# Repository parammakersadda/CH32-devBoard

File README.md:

# CH32X033F8P6 Development Board

## Purpose

This project was developed by **Param Makers Adda** to provide an open hardware development board based on the **CH32X033F8P6** microcontroller. The design is intended to be studied, modified, manufactured, and improved by anyone under the terms of the CERN Open Hardware Licence Version 2 – Weakly Reciprocal (CERN-OHL-W v2).

Copyright © 2026 Param Makers Adda

This hardware is licensed under the CERN Open Hardware Licence Version 2 – Weakly Reciprocal (CERN-OHL-W v2).

See the `LICENSE` file for the full license text.

## Images

[PCB routing](PDFs/pcb-routing.pdf)  

[Schematic](PDFs/ch32-devboard.pdf)

[3d rendering](3dModels/3dModel.stl)

## Exports

check `exports` folder for pcb export  

check the [`panelisedPcb`](panelisedPcb/) folder for panelised(multiple copies in a single board, for manufacturing purpose) pcb gerber export

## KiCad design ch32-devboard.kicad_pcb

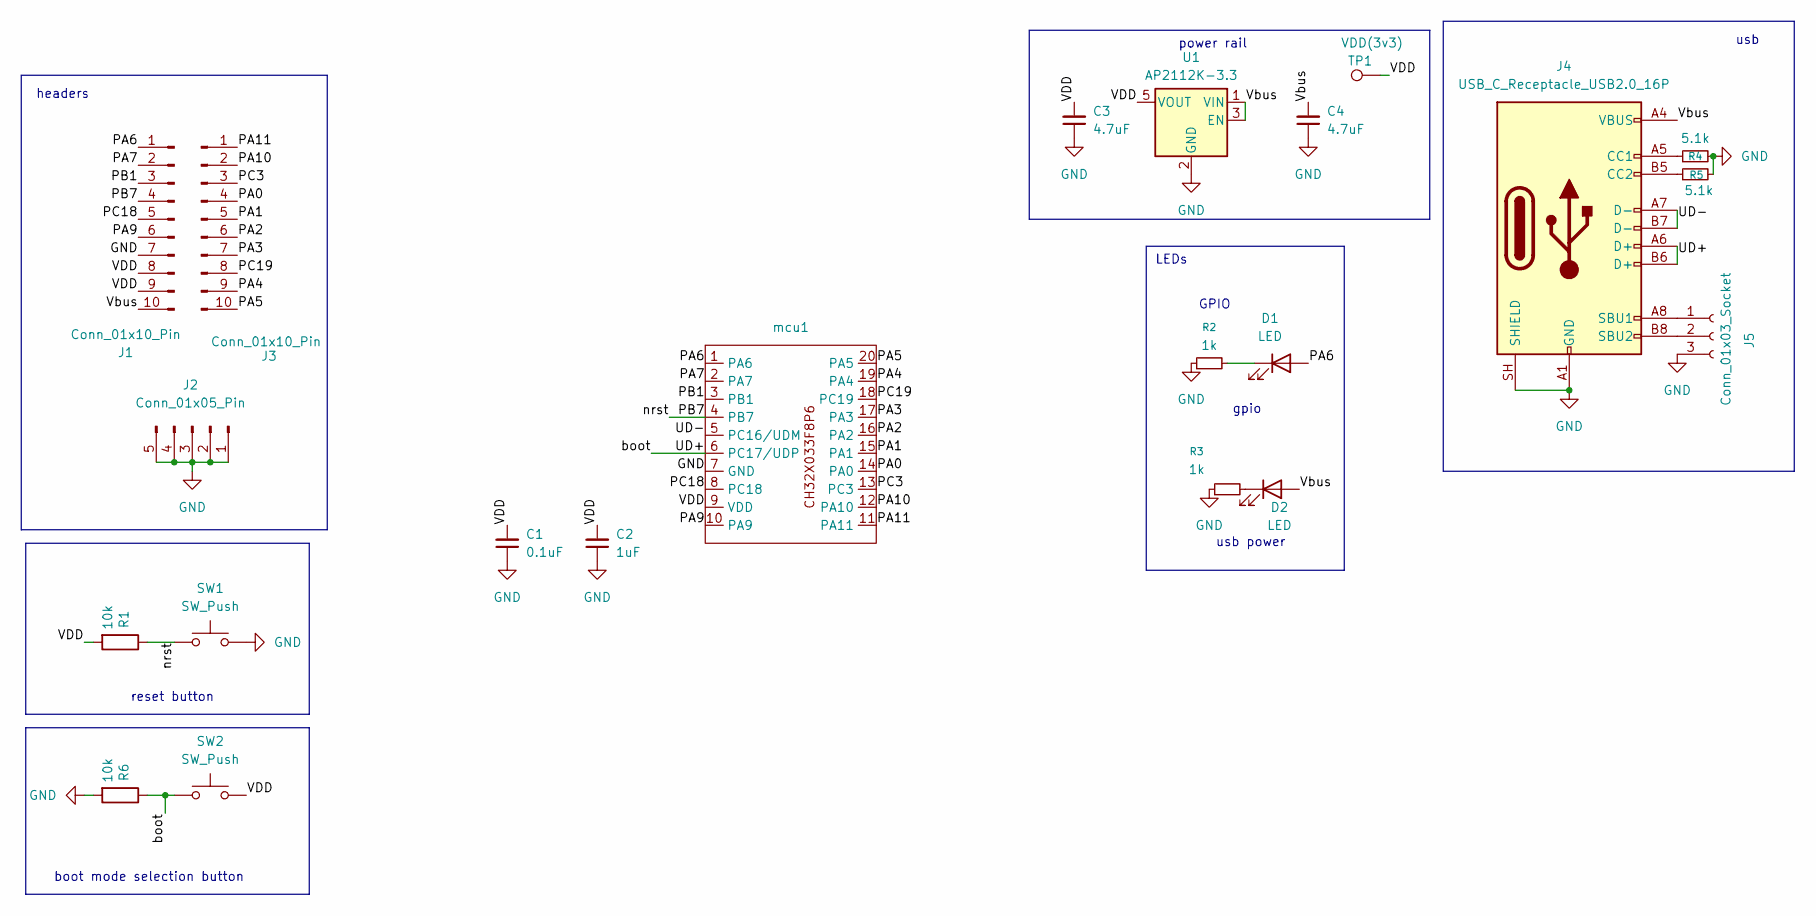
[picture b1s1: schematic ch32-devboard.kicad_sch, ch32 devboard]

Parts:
C1: 0.1uF; C_0805_2012Metric_Pad1.18x1.45mm_HandSolder
C2: 1uF; C_0805_2012Metric_Pad1.18x1.45mm_HandSolder
C3, C4: 4.7uF; C_0805_2012Metric_Pad1.18x1.45mm_HandSolder
D1, D2: LED; LED_0805_2012Metric_Pad1.15x1.40mm_HandSolder
J1, J3: Conn_01x10_Pin; PinHeader_1x10_P2.54mm_Vertical
J2: Conn_01x05_Pin; PinHeader_1x05_P2.54mm_Vertical
J4: USB_C_Receptacle_USB2.0_16P; USB_C_Receptacle_Palconn_UTC16-G
J5: Conn_01x03_Socket; PinHeader_1x03_P2.54mm_Vertical
R1, R6: 10k; R_0805_2012Metric_Pad1.20x1.40mm_HandSolder
R2, R3: 1k; R_0805_2012Metric_Pad1.20x1.40mm_HandSolder
R4, R5: 5.1k; R_0805_2012Metric_Pad1.20x1.40mm_HandSolder
SW1, SW2: SW_Push; smd-push-button-TS3425PA
TP1: VDD(3v3); TestPoint_Pad_1.0x1.0mm
U1: AP2112K-3.3; SOT-23-5
mcu1: TSSOP-20_4.4x6.5mm_P0.65mm

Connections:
/PA0: J3.4, mcu1.14 (PA0)
/PA1: J3.5, mcu1.15 (PA1)
/PA2: J3.6, mcu1.16 (PA2)
/PA3: J3.7, mcu1.17 (PA3)
/PA4: J3.9, mcu1.19 (PA4)
/PA5: J3.10, mcu1.20 (PA5)
/PA6: D1.2 (A), J1.1, mcu1.1 (PA6)
/PA7: J1.2, mcu1.2 (PA7)
/PA9: J1.6, mcu1.10 (PA9)
/PA10: J3.2, mcu1.12 (PA10)
/PA11: J3.1, mcu1.11 (PA11)
/PB1: J1.3, mcu1.3 (PB1)
/PB7: J1.4, R1.1, SW1.1, mcu1.4 (PB7)
/PC3: J3.3, mcu1.13 (PC3)
/PC18: J1.5, mcu1.8 (PC18)
/PC19: J3.8, mcu1.18 (PC19)
/UD+: J4.A6 (D+), J4.B6 (D+), R6.1, SW2.1, mcu1.6 (PC17/UDP)
/UD-: J4.A7 (D-), J4.B7 (D-), mcu1.5 (PC16/UDM)
/VDD: C1.2, C2.2, C3.2, J1.8, J1.9, R1.2, SW2.2, TP1.1 (1_1), U1.5 (VOUT), mcu1.9 (VDD)
/Vbus: C4.2, D2.2 (A), J1.10, J4.A4 (VBUS), J4.A9 (VBUS), J4.B4 (VBUS), J4.B9 (VBUS), U1.1 (VIN), U1.3 (EN)
GND: C1.1, C2.1, C3.1, C4.1, J1.7, J2.1, J2.2, J2.3, J2.4, J2.5, J4.A1 (GND), J4.A12 (GND), J4.B1 (GND), J4.B12 (GND), J4.SH (SHIELD), J5.3, R2.1, R3.1, R4.2, R5.2, R6.2, SW1.2, U1.2 (GND), mcu1.7 (GND)
unnamed: D1.1 (K), R2.2
unnamed: D2.1 (K), R3.2
unnamed: J4.A5 (CC1), R4.1
unnamed: J4.B5 (CC2), R5.1
unnamed: J4.A8 (SBU1), J5.1
unnamed: J4.B8 (SBU2), J5.2

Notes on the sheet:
headers
reset button
GPIO
usb power
usb
power rail
boot mode selection button
LEDs
gpio

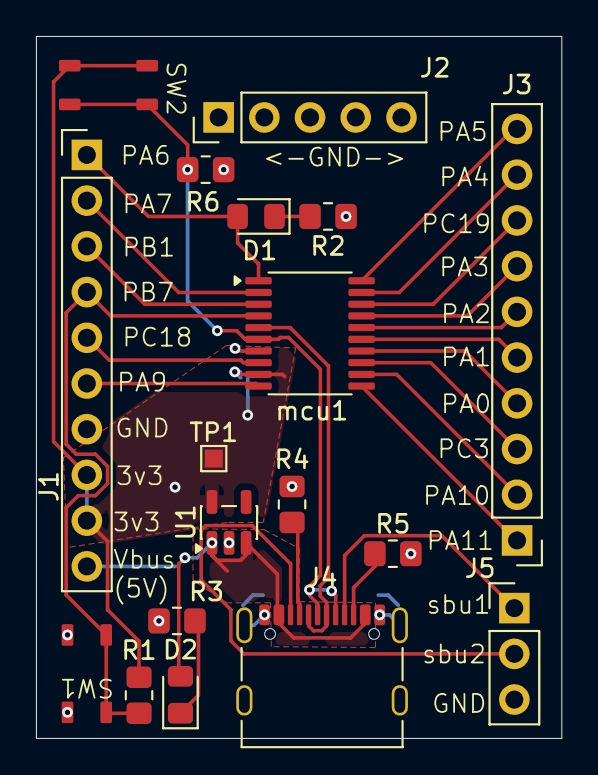
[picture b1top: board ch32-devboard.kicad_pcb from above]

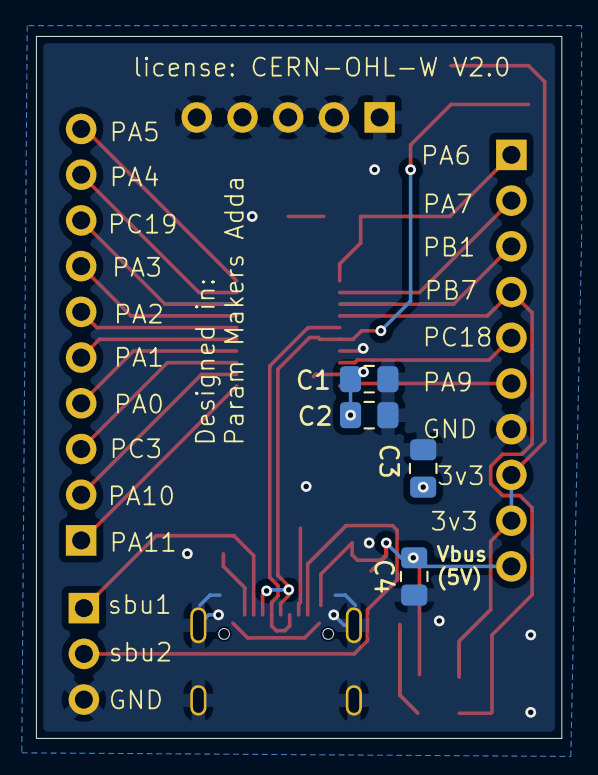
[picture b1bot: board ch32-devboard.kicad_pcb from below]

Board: 2 copper layers, 29.2 x 39.0 mm, 22 parts (4 on the bottom side), 27 nets.

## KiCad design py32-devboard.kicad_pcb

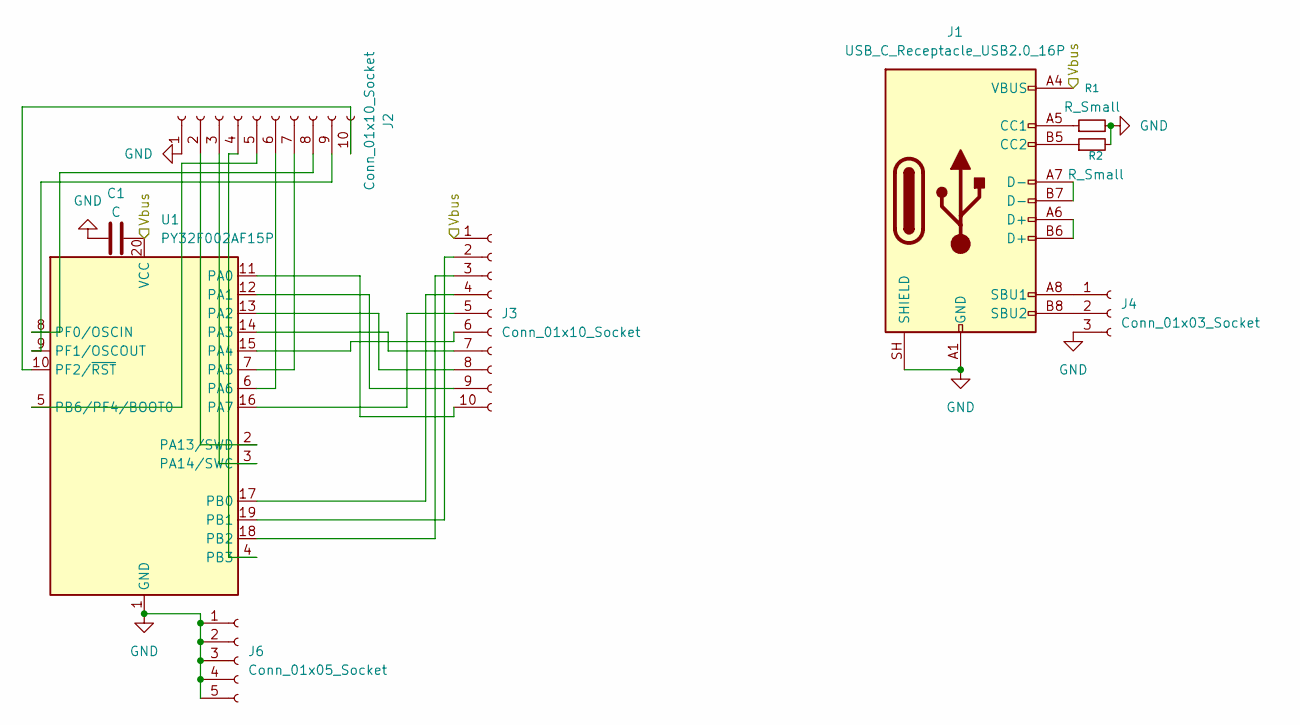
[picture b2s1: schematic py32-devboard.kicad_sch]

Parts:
C1: C; C_0805_2012Metric_Pad1.18x1.45mm_HandSolder
J1: USB_C_Receptacle_USB2.0_16P; USB_C_Receptacle_XKB_U262-16XN-4BVC11
J2, J3: Conn_01x10_Socket; PinHeader_1x10_P2.54mm_Vertical
J4: Conn_01x03_Socket; PinHeader_1x03_P2.54mm_Vertical
J6: Conn_01x05_Socket; PinHeader_1x05_P2.54mm_Vertical
R1, R2: R_Small; R_0805_2012Metric_Pad1.20x1.40mm_HandSolder
U1: PY32F002AF15P; TSSOP-20_4.4x6.5mm_P0.65mm

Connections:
/Vbus: C1.2, J1.A4 (VBUS), J1.A9 (VBUS), J1.B4 (VBUS), J1.B9 (VBUS), J3.1, U1.20 (VCC)
GND: C1.1, J1.A1 (GND), J1.A12 (GND), J1.B1 (GND), J1.B12 (GND), J1.SH (SHIELD), J2.1, J4.3, J6.1, J6.2, J6.3, J6.4, J6.5, R1.2, R2.2, U1.1 (GND)
unnamed: J1.A5 (CC1), R1.1
unnamed: J1.B5 (CC2), R2.1
unnamed: J1.A6 (D+), J1.B6 (D+)
unnamed: J1.A7 (D-), J1.B7 (D-)
unnamed: J1.A8 (SBU1), J4.1
unnamed: J1.B8 (SBU2), J4.2
unnamed: J2.2, U1.2 (PA13/SWD)
unnamed: J2.3, U1.3 (PA14/SWC)
unnamed: J2.4, U1.4 (PB3)
unnamed: J2.5, U1.5 (PB6/PF4/BOOT0)
unnamed: J2.6, U1.6 (PA6)
unnamed: J2.7, U1.7 (PA5)
unnamed: J2.8, U1.8 (PF0/OSCIN)
unnamed: J2.9, U1.9 (PF1/OSCOUT)
unnamed: J2.10, U1.10 (PF2/~RST)
unnamed: J3.2, U1.19 (PB1)
unnamed: J3.3, U1.18 (PB2)
unnamed: J3.4, U1.17 (PB0)
unnamed: J3.5, U1.16 (PA7)
unnamed: J3.6, U1.15 (PA4)
unnamed: J3.7, U1.14 (PA3)
unnamed: J3.8, U1.13 (PA2)
unnamed: J3.9, U1.12 (PA1)
unnamed: J3.10, U1.11 (PA0)

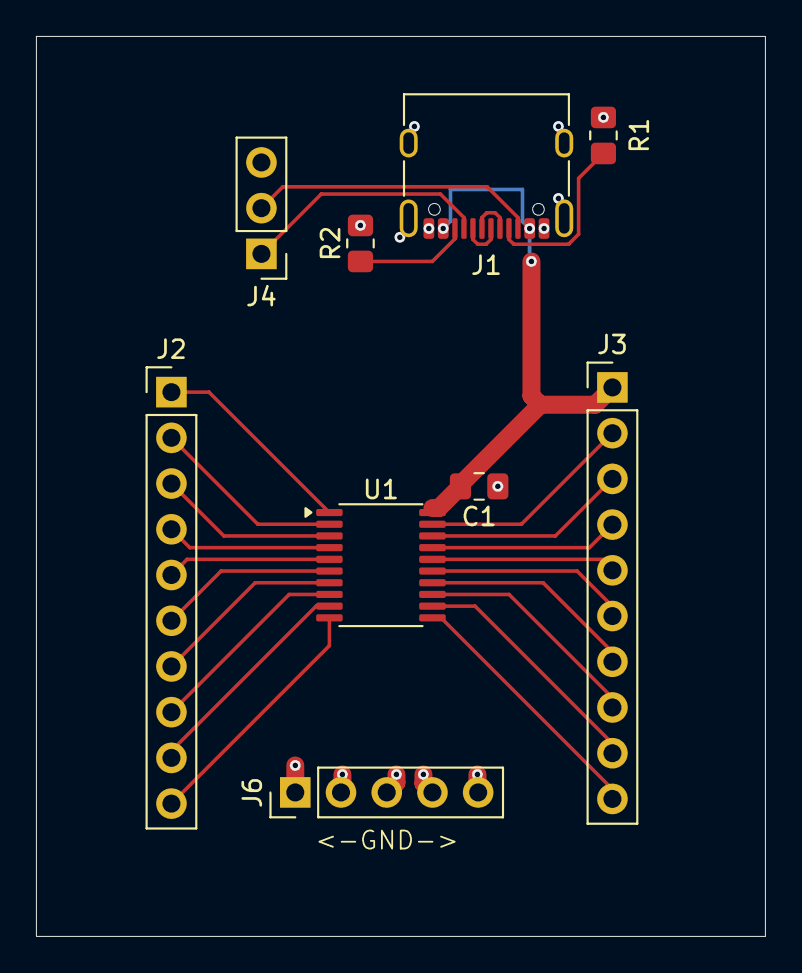
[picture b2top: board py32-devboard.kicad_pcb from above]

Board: 2 copper layers, 40.5 x 50.0 mm, 9 parts (0 on the bottom side), 26 nets.

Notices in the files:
ch32-devboard.kicad_pcb:
LICENSE: CERN-OHL-W V2.0
